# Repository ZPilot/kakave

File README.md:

# kakave
<B>- Контроллер псевдо КМД+имитация 4х дисководов для УКНЦ (на SD карте)</B></Br>

<B>Идея:</B></Br>
Сделать простой для повторения и как можно более дешевый контроллер НГМД, который будет работать со встроенным в УКНЦ драйвером.

<B>Реализация:</B></Br>
Контроллер построен на базе платы Blackpill, имеющая на борту stm32f401 или stm32f411.

<B>Что работает:</B></Br>
Чтение/запись с образов DSK размером 800 кБ, поддерживаются образы имеющие нестандартные размеры, но запись не гарантируется.
Работают: RT-11, Unix и другие ОС, программное обеспечение и игры из-под ОС.

<B>Что не работает:</B></Br>
Нет поддержки каталогов.</Br>
~~Игры от ИТО: ITO90.dsk - все игры с этого диска, ITO91.dsk - не работает PacMan.~~ (v1.1.0)

<B>Прошивка:</B></Br>
Готовые файлы записываются с адреса 0x08000000 (например, st-flash write f401test005.bin 0x08000000). Какой выбрать - по надписи на микроконтроллере Blackpill (или по chip id, который показывает st-info --probe):</Br>
- firmware401/Release/f401test005.bin - STM32F401CC (CCU6, chip id 0x423: 256 кБ flash, 64 кБ RAM). Работает и на STM32F401CE.</Br>
- firmware401/Release/f401cetest005.bin - STM32F401CE (CEU6, chip id 0x433: 512 кБ flash, 96 кБ RAM). Та же прошивка, собранная под CE: использует всю его память. На F401CC не работает.</Br>
- firmware/Release/f411test005.bin - STM32F411CE (CEU6, chip id 0x431). Для STM32F401 не подходит: работает на 100 МГц.</Br>
Все три работают с олед-дисплеями 128x64 (I2C, адрес 0x3C) на контроллерах SSD1306 (0.96"), SH1106 (1.3") и CH1116 (1.54"): тип контроллера определяется при включении по его байту состояния.</Br>
Сборка из командной строки: make (результат в build/), make release - собрать и положить в */Release/. Нужен arm-none-eabi-gcc в PATH или make TOOLCHAIN=&lt;каталог bin&gt;.</Br>
Файлы в */Release/ собраны GNU Arm Embedded 7-2018-q2-update (GCC 7.3.1, тот же компилятор, что в STM32CubeIDE 1.4): с ним make даёт точно такие же файлы. Более новые GCC (проверено 13.2) тоже собирают, но код получается другим.</Br>

<B>Ошибки:</B></Br>
На герберах перепутаны подписи под кнопками Left и Right. Кнопка Set расположена слишком близко к дисплею и мешает его установке.
В демонстрационном ролике старая модель корпуса с недостоверно подписанными светодиодными индикаторами. Индикаторы отображают сигнал "Мотор" и сигнал чтения/записи.

<B>Обратите внимание:</B></Br>
Платы BlackPill и олед-дисплея имеются в продаже с различающейся разводкой выводов.
При монтаже выводы разъема для программирования SCK и DIO запаиваются на плату.</Br>

<B>Пример работы контроллера:</B></Br>

</Br>
<B>Сообществом были произведены следующие улучшения:</B></Br>
Новая трассировка платы и гербер-файлы: <a href="Community/">Community</a></Br>
</Br>
Стильный корпус со сменными передними накладками, там же несколько моделей в сборе</Br>
</Br>
</Br>
</Br>
</Br>
</Br>
<B>Авторы модов:</B></Br>
@electroscatnes</Br>
Andrey Khristov</Br>
<B>Идейные вдохновители:<B></Br>
Alexey Kisly</Br>
@nzeemin</Br>
и все участники канала: <a href="https://t.me/MC0511UKNC">https://t.me/MC0511UKNC</a>

## CHANGELOG

v1.1.0 Правки
- исправлена ошибка загрузки игр с ITO дисков
- добавлена поддержка больших экранов на чипе CH1116

v1.0.0 Исходная публичная версия

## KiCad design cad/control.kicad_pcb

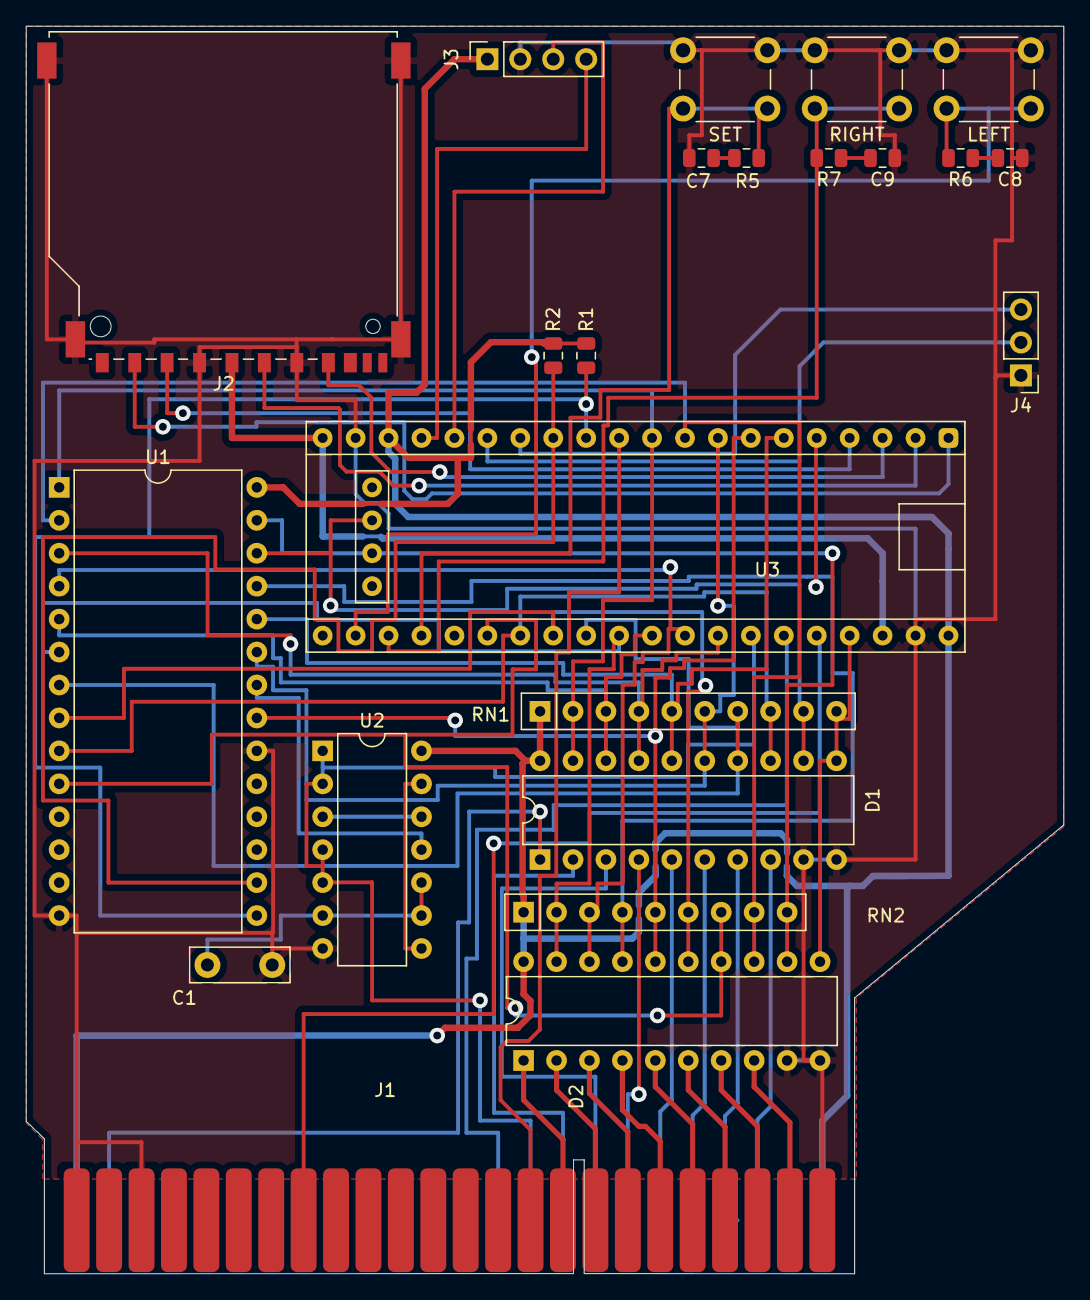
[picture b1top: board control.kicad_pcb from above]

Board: 2 copper layers, 80.0 x 96.2 mm, 23 parts (0 on the bottom side), 60 nets.

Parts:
C1: 300pF; C_Disc_D7.5mm_W2.5mm_P5.00mm
C7, C8, C9: 100nF; C_0805_2012Metric
D1, D2: k580va87; DIP-20_W7.62mm
J1: con_snp_15; snp15
J2: SD_Card; SD_TE_2041021
J3: SSD_1306; PinSocket_1x04_P2.54mm_Vertical
J4: UART; PinHeader_1x03_P2.54mm_Vertical
LEFT: SW_LEFT; SW_PUSH_6mm_H7.3mm
R1, R2: 3.3k; R_0805_2012Metric
R5, R6, R7: 100; R_0805_2012Metric
RIGHT: SW_RIGHT; SW_PUSH_6mm_H7.3mm
RN1: R_Network08; R_Array_SIP10
RN2: R_Network08; R_Array_SIP9
SET: SW_SET; SW_PUSH_6mm_H7.3mm
U1: 27C512; DIP-28_W15.24mm
U2: 7400; DIP-14_W7.62mm
U3: BlackPill_F401

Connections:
+3V3: J2.4, U3.20, U3.23
+5V: D1.20, D2.20, J1.A1, J1.A24, J3.1, R1.1, R2.1, RN1.1, RN2.1, U1.28, U2.14, U3.18, U3.21
/#OE: U1.22, U2.11
/AD0: D2.6, J1.B21
/AD1: D1.7, J1.A21
/AD2: D2.5, J1.B20
/AD3: D1.6, J1.A20
/AD4: D2.1, J1.B16
/AD5: D1.2, J1.A16
/AD6: D2.2, J1.B17
/AD7: D1.3, J1.A17
/AD8: D2.3, J1.B18
/AD9: D1.4, J1.A18
/AD10: D2.4, J1.B19
/AD11: D1.5, J1.A19
/AD12: D2.7, J1.B22
/AD13: D1.8, J1.A22
/AD14: D2.8, J1.B23
/AD15: D1.1, J1.A2
/BAD0: D2.14, RN2.7, U1.10, U3.35
/BAD1: D1.13, RN1.8, U1.9, U3.34
/BAD2: D2.15, RN2.6, U1.8, U3.33
/BAD3: D1.14, RN1.7, U1.7, U3.32
/BAD4: D2.19, RN2.2, U1.6, U3.31
/BAD5: D1.18, RN1.3, U1.5, U3.30
/BAD6: D2.18, RN2.3, U1.4, U3.29
/BAD7: D1.17, RN1.4, U1.3, U3.28
/BAD8: D2.17, RN2.4, U1.25, U3.5
/BAD9: D1.16, RN1.5, U1.24, U3.6
/BAD10: D2.16, RN2.5, U1.21, U3.7
/BAD11: D1.15, RN1.6, U1.23, U3.8
/BAD12: D2.13, RN2.8, U1.2, U3.9
/BAD13: D1.12, RN1.9, U1.26, U3.42
/BAD14: D2.12, RN2.9, U1.27, U3.43
/BAD15: D1.19, RN1.2, U1.1, U3.10
/DIN: J1.A14, U3.26
/DOUT: J1.B8, U3.25
/I2C_SCL: J3.3, U3.16
/I2C_SDA: J3.4, U3.17
/LEFT_BTN: LEFT.1, R6.2, U3.39
/RIGHT_BTN: R7.2, RIGHT.1, U3.38
/RPLY: J1.B15, U3.11
/SELECT1: R1.2, U1.15, U3.12
/SELECT2: R2.2, U1.16, U3.13
/SET_BTN: R5.2, SET.1, U3.37
/SPI2_CS: J2.1, U3.1
/SPI2_MISO: J2.7, U3.3
/SPI2_MOSI: J2.2, U3.4
/SPI2_SCK: J2.5, U3.2
/SYNC: J1.A15, U2.1, U2.2, U2.4, U2.5, U3.27
/UART_RX: J4.2, U3.15
/UART_TX: J4.3, U3.14
/VA87DIR: D1.11, D2.11, RN1.10, U3.24
GND: C1.2, C7.1, C8.1, C9.1, D1.9, D1.10, D2.9, D2.10, J1.B1, J1.B3, J1.B24, J2.3, J2.6, J2.12, J3.2, J4.1, LEFT.2, RIGHT.2, SET.2, U1.14, U1.20, U2.7, U3.19, U3.22
unnamed: C1.1, U2.6, U2.9, U2.10
unnamed: C7.2, R5.1
unnamed: C8.2, R6.1
unnamed: C9.2, R7.1
unnamed: U2.3, U2.12
unnamed: U2.8, U2.13

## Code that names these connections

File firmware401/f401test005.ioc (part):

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Mcu.Name=STM32F401C(B-C)Ux
Mcu.Package=UFQFPN48
Mcu.UserName=STM32F401CCUx
PA0-WKUP.GPIOParameters=GPIO_Speed,PinState,GPIO_ModeDefaultOutputPP
PA0-WKUP.GPIO_ModeDefaultOutputPP=GPIO_MODE_OUTPUT_OD
PA0-WKUP.GPIO_Speed=GPIO_SPEED_FREQ_VERY_HIGH
PA0-WKUP.PinState=GPIO_PIN_SET
PA0-WKUP.Signal=GPIO_Output
PA1.GPIOParameters=GPIO_Speed,PinState,GPIO_ModeDefaultOutputPP
PA1.GPIO_ModeDefaultOutputPP=GPIO_MODE_OUTPUT_OD
PA1.GPIO_Speed=GPIO_SPEED_FREQ_VERY_HIGH
PA1.PinState=GPIO_PIN_SET
PA1.Signal=GPIO_Output
PA10.GPIOParameters=GPIO_Speed,PinState,GPIO_ModeDefaultOutputPP
PA10.GPIO_ModeDefaultOutputPP=GPIO_MODE_OUTPUT_OD
PA10.GPIO_Speed=GPIO_SPEED_FREQ_VERY_HIGH
PA10.PinState=GPIO_PIN_SET
PA10.Signal=GPIO_Output
PA11.GPIOParameters=GPIO_Speed,PinState,GPIO_ModeDefaultOutputPP
PA11.GPIO_ModeDefaultOutputPP=GPIO_MODE_OUTPUT_OD
PA11.GPIO_Speed=GPIO_SPEED_FREQ_VERY_HIGH
PA11.PinState=GPIO_PIN_SET
PA11.Signal=GPIO_Output
PA12.GPIOParameters=GPIO_Speed,PinState,GPIO_ModeDefaultOutputPP
PA12.GPIO_ModeDefaultOutputPP=GPIO_MODE_OUTPUT_OD
PA12.GPIO_Speed=GPIO_SPEED_FREQ_VERY_HIGH
PA12.PinState=GPIO_PIN_SET
PA12.Signal=GPIO_Output
PA13.GPIOParameters=GPIO_Speed,PinState,GPIO_ModeDefaultOutputPP
PA13.GPIO_ModeDefaultOutputPP=GPIO_MODE_OUTPUT_OD
PA13.GPIO_Speed=GPIO_SPEED_FREQ_VERY_HIGH
PA13.PinState=GPIO_PIN_SET
PA13.Signal=GPIO_Output
PA14.GPIOParameters=GPIO_Speed,PinState,GPIO_ModeDefaultOutputPP
PA14.GPIO_ModeDefaultOutputPP=GPIO_MODE_OUTPUT_OD
PA14.GPIO_Speed=GPIO_SPEED_FREQ_VERY_HIGH
PA14.PinState=GPIO_PIN_SET
PA14.Signal=GPIO_Output
PA15.GPIOParameters=GPIO_Speed,PinState,GPIO_ModeDefaultOutputPP
PA15.GPIO_ModeDefaultOutputPP=GPIO_MODE_OUTPUT_OD
PA15.GPIO_Speed=GPIO_SPEED_FREQ_VERY_HIGH
PA15.PinState=GPIO_PIN_SET
PA15.Signal=GPIO_Output
PA2.GPIOParameters=GPIO_Speed,PinState,GPIO_ModeDefaultOutputPP
PA2.GPIO_ModeDefaultOutputPP=GPIO_MODE_OUTPUT_OD
PA2.GPIO_Speed=GPIO_SPEED_FREQ_VERY_HIGH
PA2.PinState=GPIO_PIN_SET
PA2.Signal=GPIO_Output
PA3.GPIOParameters=GPIO_Speed,PinState,GPIO_ModeDefaultOutputPP
PA3.GPIO_ModeDefaultOutputPP=GPIO_MODE_OUTPUT_OD
PA3.GPIO_Speed=GPIO_SPEED_FREQ_VERY_HIGH
PA3.PinState=GPIO_PIN_SET
PA3.Signal=GPIO_Output
PA4.GPIOParameters=GPIO_Speed,PinState,GPIO_ModeDefaultOutputPP
PA4.GPIO_ModeDefaultOutputPP=GPIO_MODE_OUTPUT_OD
PA4.GPIO_Speed=GPIO_SPEED_FREQ_VERY_HIGH
PA4.PinState=GPIO_PIN_SET
PA4.Signal=GPIO_Output
PA5.GPIOParameters=GPIO_Speed,PinState,GPIO_ModeDefaultOutputPP
PA5.GPIO_ModeDefaultOutputPP=GPIO_MODE_OUTPUT_OD
PA5.GPIO_Speed=GPIO_SPEED_FREQ_VERY_HIGH
PA5.PinState=GPIO_PIN_SET
PA5.Signal=GPIO_Output
PA6.GPIOParameters=GPIO_Speed,PinState,GPIO_ModeDefaultOutputPP
PA6.GPIO_ModeDefaultOutputPP=GPIO_MODE_OUTPUT_OD
PA6.GPIO_Speed=GPIO_SPEED_FREQ_VERY_HIGH
PA6.PinState=GPIO_PIN_SET
PA6.Signal=GPIO_Output
PA7.GPIOParameters=GPIO_Speed,PinState,GPIO_ModeDefaultOutputPP
PA7.GPIO_ModeDefaultOutputPP=GPIO_MODE_OUTPUT_OD
PA7.GPIO_Speed=GPIO_SPEED_FREQ_VERY_HIGH
PA7.PinState=GPIO_PIN_SET
PA7.Signal=GPIO_Output
PA8.GPIOParameters=GPIO_Speed,PinState,GPIO_ModeDefaultOutputPP
PA8.GPIO_ModeDefaultOutputPP=GPIO_MODE_OUTPUT_OD
PA8.GPIO_Speed=GPIO_SPEED_FREQ_VERY_HIGH
PA8.PinState=GPIO_PIN_SET
PA8.Signal=GPIO_Output
PA9.GPIOParameters=GPIO_Speed,PinState,GPIO_ModeDefaultOutputPP
PA9.GPIO_ModeDefaultOutputPP=GPIO_MODE_OUTPUT_OD
PA9.GPIO_Speed=GPIO_SPEED_FREQ_VERY_HIGH
PA9.PinState=GPIO_PIN_SET
PA9.Signal=GPIO_Output
PB0.GPIOParameters=GPIO_Label
PB0.GPIO_Label=SYNC
PB0.Signal=GPIO_Input
PB1.GPIOParameters=GPIO_Label
PB1.GPIO_Label=DIN
PB1.Signal=GPIO_Input
PB10.GPIOParameters=GPIO_Speed,PinState,GPIO_Label,GPIO_ModeDefaultOutputPP
PB10.GPIO_Label=VA87DIR
PB10.GPIO_ModeDefaultOutputPP=GPIO_MODE_OUTPUT_OD
PB10.GPIO_Speed=GPIO_SPEED_FREQ_VERY_HIGH
PB10.PinState=GPIO_PIN_SET
PB10.Signal=GPIO_Output
PB12.GPIOParameters=GPIO_Speed,GPIO_PuPd,GPIO_Label
PB12.GPIO_Label=SPI2_CS
PB12.GPIO_PuPd=GPIO_NOPULL
PB12.GPIO_Speed=GPIO_SPEED_FREQ_VERY_HIGH
PB12.Signal=GPIO_Output
PB13.GPIOParameters=GPIO_Speed,GPIO_PuPd
PB13.GPIO_PuPd=GPIO_PULLUP
PB13.GPIO_Speed=GPIO_SPEED_FREQ_VERY_HIGH
PB13.Mode=Full_Duplex_Master
PB13.Signal=SPI2_SCK
PB14.GPIOParameters=GPIO_Speed,GPIO_PuPd
PB14.GPIO_PuPd=GPIO_PULLUP
PB14.GPIO_Speed=GPIO_SPEED_FREQ_VERY_HIGH
PB14.Mode=Full_Duplex_Master
PB14.Signal=SPI2_MISO
PB15.GPIOParameters=GPIO_Speed,GPIO_PuPd
PB15.GPIO_PuPd=GPIO_PULLUP
PB15.GPIO_Speed=GPIO_SPEED_FREQ_VERY_HIGH
PB15.Mode=Full_Duplex_Master
PB15.Signal=SPI2_MOSI
PB2.GPIOParameters=GPIO_Label
PB2.GPIO_Label=DOUT
PB2.Signal=GPIO_Input
PB3.GPIOParameters=GPIO_Speed,PinState,GPIO_Label,GPIO_ModeDefaultOutputPP
PB3.GPIO_Label=RPLY
PB3.GPIO_ModeDefaultOutputPP=GPIO_MODE_OUTPUT_OD
PB3.GPIO_Speed=GPIO_SPEED_FREQ_VERY_HIGH
PB3.PinState=GPIO_PIN_SET
PB3.Signal=GPIO_Output
PB4.GPIOParameters=GPIO_Label,GPIO_ModeDefaultEXTI
PB4.GPIO_Label=SEL1
PB4.GPIO_ModeDefaultEXTI=GPIO_MODE_IT_FALLING
PB4.Signal=GPXTI4
PB5.GPIOParameters=GPIO_Label,GPIO_ModeDefaultEXTI
PB5.GPIO_Label=SEL2
PB5.GPIO_ModeDefaultEXTI=GPIO_MODE_IT_FALLING
PB5.Signal=GPXTI5
PB6.GPIOParameters=GPIO_Speed,GPIO_Label
PB6.GPIO_Label=LED1
PB6.GPIO_Speed=GPIO_SPEED_FREQ_VERY_HIGH
PB6.Signal=GPIO_Output
PB7.GPIOParameters=GPIO_Speed,GPIO_Label
PB7.GPIO_Label=LED2
PB7.GPIO_Speed=GPIO_SPEED_FREQ_VERY_HIGH
PB7.Signal=GPIO_Output
PB8.Mode=I2C
PB8.Signal=I2C1_SCL
PB9.Mode=I2C
PB9.Signal=I2C1_SDA
PC13-ANTI_TAMP.GPIOParameters=GPIO_PuPd,GPIO_Label
PC13-ANTI_TAMP.GPIO_Label=LFL_BTN
PC13-ANTI_TAMP.GPIO_PuPd=GPIO_PULLUP
PC13-ANTI_TAMP.Signal=GPIO_Input
PC14-OSC32_IN.GPIOParameters=GPIO_PuPd,GPIO_Label
PC14-OSC32_IN.GPIO_Label=RGT_BTN
PC14-OSC32_IN.GPIO_PuPd=GPIO_PULLUP
PC14-OSC32_IN.Signal=GPIO_Input
PC15-OSC32_OUT.GPIOParameters=GPIO_PuPd,GPIO_Label
PC15-OSC32_OUT.GPIO_Label=SET_BTN
PC15-OSC32_OUT.GPIO_PuPd=GPIO_PULLUP
PC15-OSC32_OUT.Signal=GPIO_Input
PH0\ -\ OSC_IN.Mode=HSE-External-Oscillator
PH0\ -\ OSC_IN.Signal=RCC_OSC_IN
PH1\ -\ OSC_OUT.Mode=HSE-External-Oscillator
PH1\ -\ OSC_OUT.Signal=RCC_OSC_OUT
RCC.HSE_VALUE=25000000
RCC.SYSCLKFreq_VALUE=84000000
RCC.SYSCLKSource=RCC_SYSCLKSOURCE_PLLCLK
board=custom

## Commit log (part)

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2020-09-29 for stm32f411
2020-09-29 for stm32f401
2020-09-29 KiCAD files
2020-09-29 photo
2020-09-29 Delete ctrl128a (копия).s_
    Modify
2020-10-02 case stl files
2020-10-08 27c512
2020-10-10 GRBL
2020-10-13 case
2023-04-03 Author Denis Nikolaevich
2023-04-24 Community
2023-06-22 the latest version of the board and case
